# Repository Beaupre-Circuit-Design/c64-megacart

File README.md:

# MegaCart 64

# Introduction

An open-source generic eprom cartridge for the Commodore 64, configurable as an 8K/16K and 8K/16K Ultimax cartridge. The main difference with other design are compatibility with 28 and 32 pin rom chips, allowing newer/current eeprom/flash to be used while keeping compatibilty with older devices.

# Compatibility

The design is comparable to BWACK's Versa64Cart and has the same basic limitations (no software bank switching capabilities) and therefore is not suitable as a Kernal replacement or cartridge that use more than 16K of rom.

# Configuration

## J1 - Device Size

Set J1 accordingly to the device used (28 or 32 pin).

## J2 - Rom Size

Set J2 to the rom image size (8K or 16K).

## J3 - CE CTRL

J3 should always be set to LOW, unless you have very special needs.

## SW2/J4 - Mode Select

Cartridge mode is set by both SW2 and J4, the following table list all the possible modes:

|Mode         |GAME   |EXROM  |ROML   |ROMH   |16K    |C64 Address Space             |
|:-----------:|:-----:|:-----:|:-----:|:-----:|:-----:|:----------------------------:|
|8K           |HIGH   |LOW    |Short  |       |       |0x8000-0x9FFF                 |
|8K Ultimax   |LOW    |HIGH   |       |Short  |       |0xE000-0xFFFF                 |
|16K          |LOW    |LOW    |       |       |Short  |0x8000-0xBFFF                 |
|16K Ultimax  |LOW    |HIGH   |       |       |Short  |0x8000-0x9FFF, 0xE000-0XFFFF  |

In Ultimax cartridge mode, the Kernal ROM (0xE000 – 0xFFFF) is replaced by the content of the EPROM of the MegaCart-64. When the 6510 CPU reset, it jump to the Reset vector located at 0xFFFC and 0xFFFD. the software in the EPROM will completely take control of the computer, allowing cartridge like the C64 Dead Test to work.

In normal cartridge mode, the C64 Kernal check memory location 0x8004-0x8008 for the cartridge signature CBM80 (PETSCII 0xC3, 0xC2, 0xCD, 0x38, 0x30), if found the Kernal will jump to the cartridge cold start vector (0x8000-0x8001).

## SW1 - Bank Switching

Bank switching of the EPROM is done by SW1 accordingly to this table (in 16K mode, A13 is ignored), up to 64 8k banks or 32 16K banks are available using a AT29C040 or similar EEPROM.

|Mode   |A13  |A14  |A15  |A16  |A17  |A18  | Start of Bank   |
|:-----:|:---:|:---:|:---:|:---:|:---:|:---:|:---------------:|
|8/16K  |     |     |     |     |     |     |0x00000          |
|8K     |  X  |     |     |     |     |     |0x02000          |
|8/16K  |     |  X  |     |     |     |     |0x04000          |
|8K     |  X  |  X  |     |     |     |     |0x06000          |
|8/16K  |     |     |  X  |     |     |     |0x08000          |
|8K     |  X  |     |  X  |     |     |     |0x0A000          |
|8/16K  |     |  X  |  X  |     |     |     |0x0C000          |
|8K     |  X  |  X  |  X  |     |     |     |0x0E000          |
...
|8/16K  |     |     |     |  X  |     |     |0x10000          |
...
|8/16K  |     |     |     |     |  X  |     |0x20000          |
...
|8/16K  |     |     |     |  X  |  X  |     |0x30000          |
...
|8/16K  |     |     |     |     |     |  X  |0x40000          |
...
|8/16K  |     |     |     |  X  |     |  X  |0x50000          |
...
|8/16K  |     |     |     |     |  X  |  X  |0x60000          |
...
|8/16K  |     |     |     |  X  |  X  |  X  |0x70000          |
...
|8/16K  |     |     |  X  |  X  |  X  |  X  |0x78000          |
|8K     |  X  |     |  X  |  X  |  X  |  X  |0x7A000          |
|8/16K  |     |  X  |  X  |  X  |  X  |  X  |0x7C000          |
|8K     |  X  |  X  |  X  |  X  |  X  |  X  |0x7E000          |

# Components and assembly

[Gerbers files](Gerbers/) are available for uploading to your prefered manufacturer (I personnally use JLCPCB). In adition to the PCB, a few components must be sourced. If you want to save a few cents or don't want to use Dip-Switch, SW1 can be replace by a 2x6 male header and SW2 with a 2x2 male header. The values of R1-R8 are not critical, anything over 1K will probably work just fine too. As usual, start with the smallest components and build up (in this case, the sockets and capacitors are probably the smallest height you will have).

|Designator|Value                                |Total Quantity|
|----------|-------------------------------------|--------------|
|C1        |Ceramic Capacitor 100nF              |1             |
|R1-R8     |10K Resistor                         |8             |
|D1-D2     |1N4148 Diode                         |2             |
|U1        |32 pin Dip Socket                    |1             |
|SW1       |Dip Switch 6 Positions               |1             |
|SW2       |Dip Switch 2 Positions               |1             |
|J1-J4     |13 pin Male Header (cut as needed)   |1             |
|PB1       |Push button momentary 6mm            |1             |

Once everything is assembled, program your eprom, configure the board and you're done.

# Licence

This work is licensed under the Creative Commons Attribution-NonCommercial-ShareAlike 4.0 International License. To view a copy of this license, visit http://creativecommons.org/licenses/by-nc-sa/4.0/ or send a letter to Creative Commons, PO Box 1866, Mountain View, CA 94042, USA.

# Revision History

|Revision  |Description                    |
|:--------:|-------------------------------|
|1.0       |Initial prototype              |
|2.0       |Reduce size, revised silkscreen|

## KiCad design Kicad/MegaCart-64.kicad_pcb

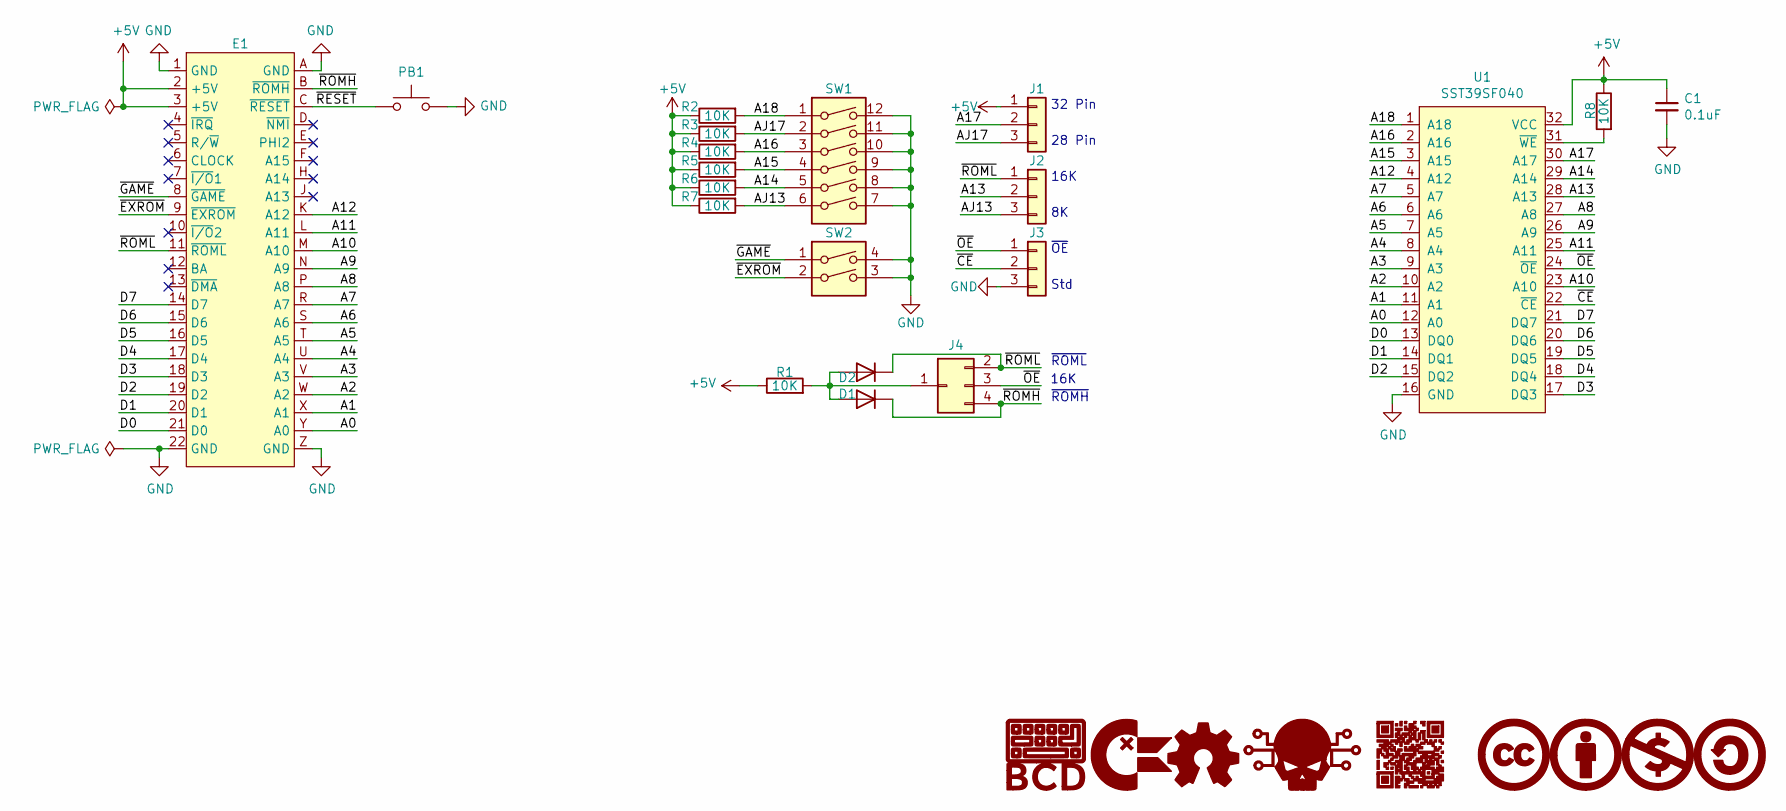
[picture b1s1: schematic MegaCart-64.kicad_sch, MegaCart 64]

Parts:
C1: 0.1uF; C_Disc_D3.8mm_W2.6mm_P2.50mm
D1, D2: 1N4148; D_DO-35_SOD27_P2.54mm_Vertical_AnodeUp
E1: Cartrige_Edge_Connector
G1: BCD_Logo; BCD_Logo_5mm
G2: ChickenLips; ChickenLips_2.5mm
G3: OpenSource_Hardware; Open_Source_Hardware_2.5mm
G4: BDC_QR; BDC_QR_10mm
G5: Skull; Skull_2.5mm
G6: CreativeCommons; CreativeCommons_2.5mm
G7: CreativeCommons_Attribution; CreativeCommons_Attribution_2.5mm
G8: CreativeCommons_NonCommercial; CreativeCommons_NonCommercial_2.5mm
G9: CreativeCommons_ShareAlike; CreativeCommons_ShareAlike_2.5mm
J1, J2, J3: Conn_01x03; PinHeader_1x03_P2.54mm_Vertical
J4: Conn_Tri-State; PinHeader_T-Shaped_Tri-State_P2.54mm_Vertical
PB1: SW_Push_Dual; SW_PUSH_6mm
R1, R2, R3, R4, R5, R6, R7, R8: 10K; R_Axial_DIN0207_L6.3mm_D2.5mm_P2.54mm_Vertical
SW1: SW_DIP_x06; Combo_PinHeader_SW_DIP_SPSTx06_Slide_9.78x17.42mm_W7.62mm_P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
SW2: SW_DIP_x02; Combo_PinHeader_SW_DIP_SPSTx02_Slide_9.78x7.26mm_W7.62mm_P2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
U1: SST39SF040; DIP-32_W15.24mm_Socket

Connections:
+5V: C1.1, E1.2 (+5V), E1.3 (+5V), J1.1, R1.1, R2.1, R3.1, R4.1, R5.1, R6.1, R7.1, R8.1, U1.32 (VCC)
/A0: E1.Y (A0), U1.12 (A0)
/A1: E1.X (A1), U1.11 (A1)
/A2: E1.W (A2), U1.10 (A2)
/A3: E1.V (A3), U1.9 (A3)
/A4: E1.U (A4), U1.8 (A4)
/A5: E1.T (A5), U1.7 (A5)
/A6: E1.S (A6), U1.6 (A6)
/A7: E1.R (A7), U1.5 (A7)
/A8: E1.P (A8), U1.27 (A8)
/A9: E1.N (A9), U1.26 (A9)
/A10: E1.M (A10), U1.23 (A10)
/A11: E1.L (A11), U1.25 (A11)
/A12: E1.K (A12), U1.4 (A12)
/A13: J2.2, U1.28 (A13)
/A14: R6.2, SW1.5, U1.29 (A14)
/A15: R5.2, SW1.4, U1.3 (A15)
/A16: R4.2, SW1.3, U1.2 (A16)
/A17: J1.2, U1.30 (A17)
/A18: R2.2, SW1.1, U1.1 (A18)
/AJ13: J2.3, R7.2, SW1.6
/AJ17: J1.3, R3.2, SW1.2
/D0: E1.21 (D0), U1.13 (DQ0)
/D1: E1.20 (D1), U1.14 (DQ1)
/D2: E1.19 (D2), U1.15 (DQ2)
/D3: E1.18 (D3), U1.17 (DQ3)
/D4: E1.17 (D4), U1.18 (DQ4)
/D5: E1.16 (D5), U1.19 (DQ5)
/D6: E1.15 (D6), U1.20 (DQ6)
/D7: E1.14 (D7), U1.21 (DQ7)
/~CE: J3.2, U1.22 (~CE)
/~EXROM: E1.9 (~EXROM), SW2.2
/~GAME: E1.8 (~GAME), SW2.1
/~OE: J3.1, J4.3, U1.24 (~OE)
/~RESET: E1.C (~RESET), PB1.1
/~ROMH: D1.1 (K), E1.B (~ROMH), J4.4
/~ROML: D2.1 (K), E1.11 (~ROML), J2.1, J4.2
GND: C1.2, E1.1 (GND), E1.22 (GND), E1.A (GND), E1.Z (GND), J3.3, PB1.2, SW1.7, SW1.8, SW1.9, SW1.10, SW1.11, SW1.12, SW2.3, SW2.4, U1.16 (GND)
unnamed: D1.2 (A), D2.2 (A), J4.1, R1.2
unnamed: R8.2, U1.31 (~WE)

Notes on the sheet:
32 Pin
Std
~{ROML}
~{ROMH}
~{OE}
16K
28 Pin

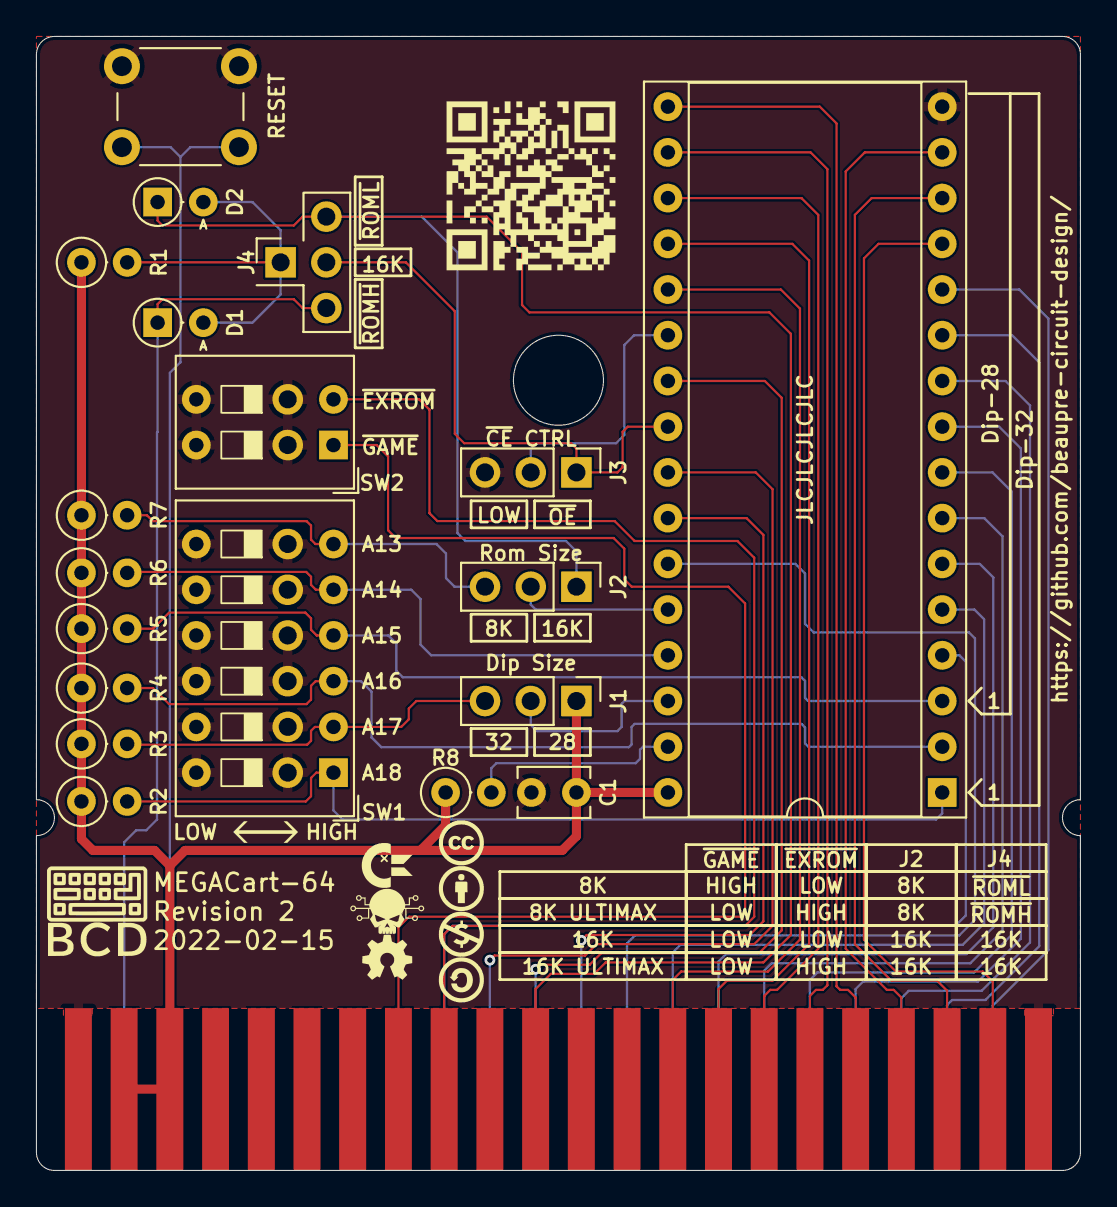
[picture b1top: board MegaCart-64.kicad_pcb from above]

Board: 2 copper layers, 58.0 x 63.0 mm, 29 parts (0 on the bottom side), 40 nets.

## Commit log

2022-03-09 Added revision history
